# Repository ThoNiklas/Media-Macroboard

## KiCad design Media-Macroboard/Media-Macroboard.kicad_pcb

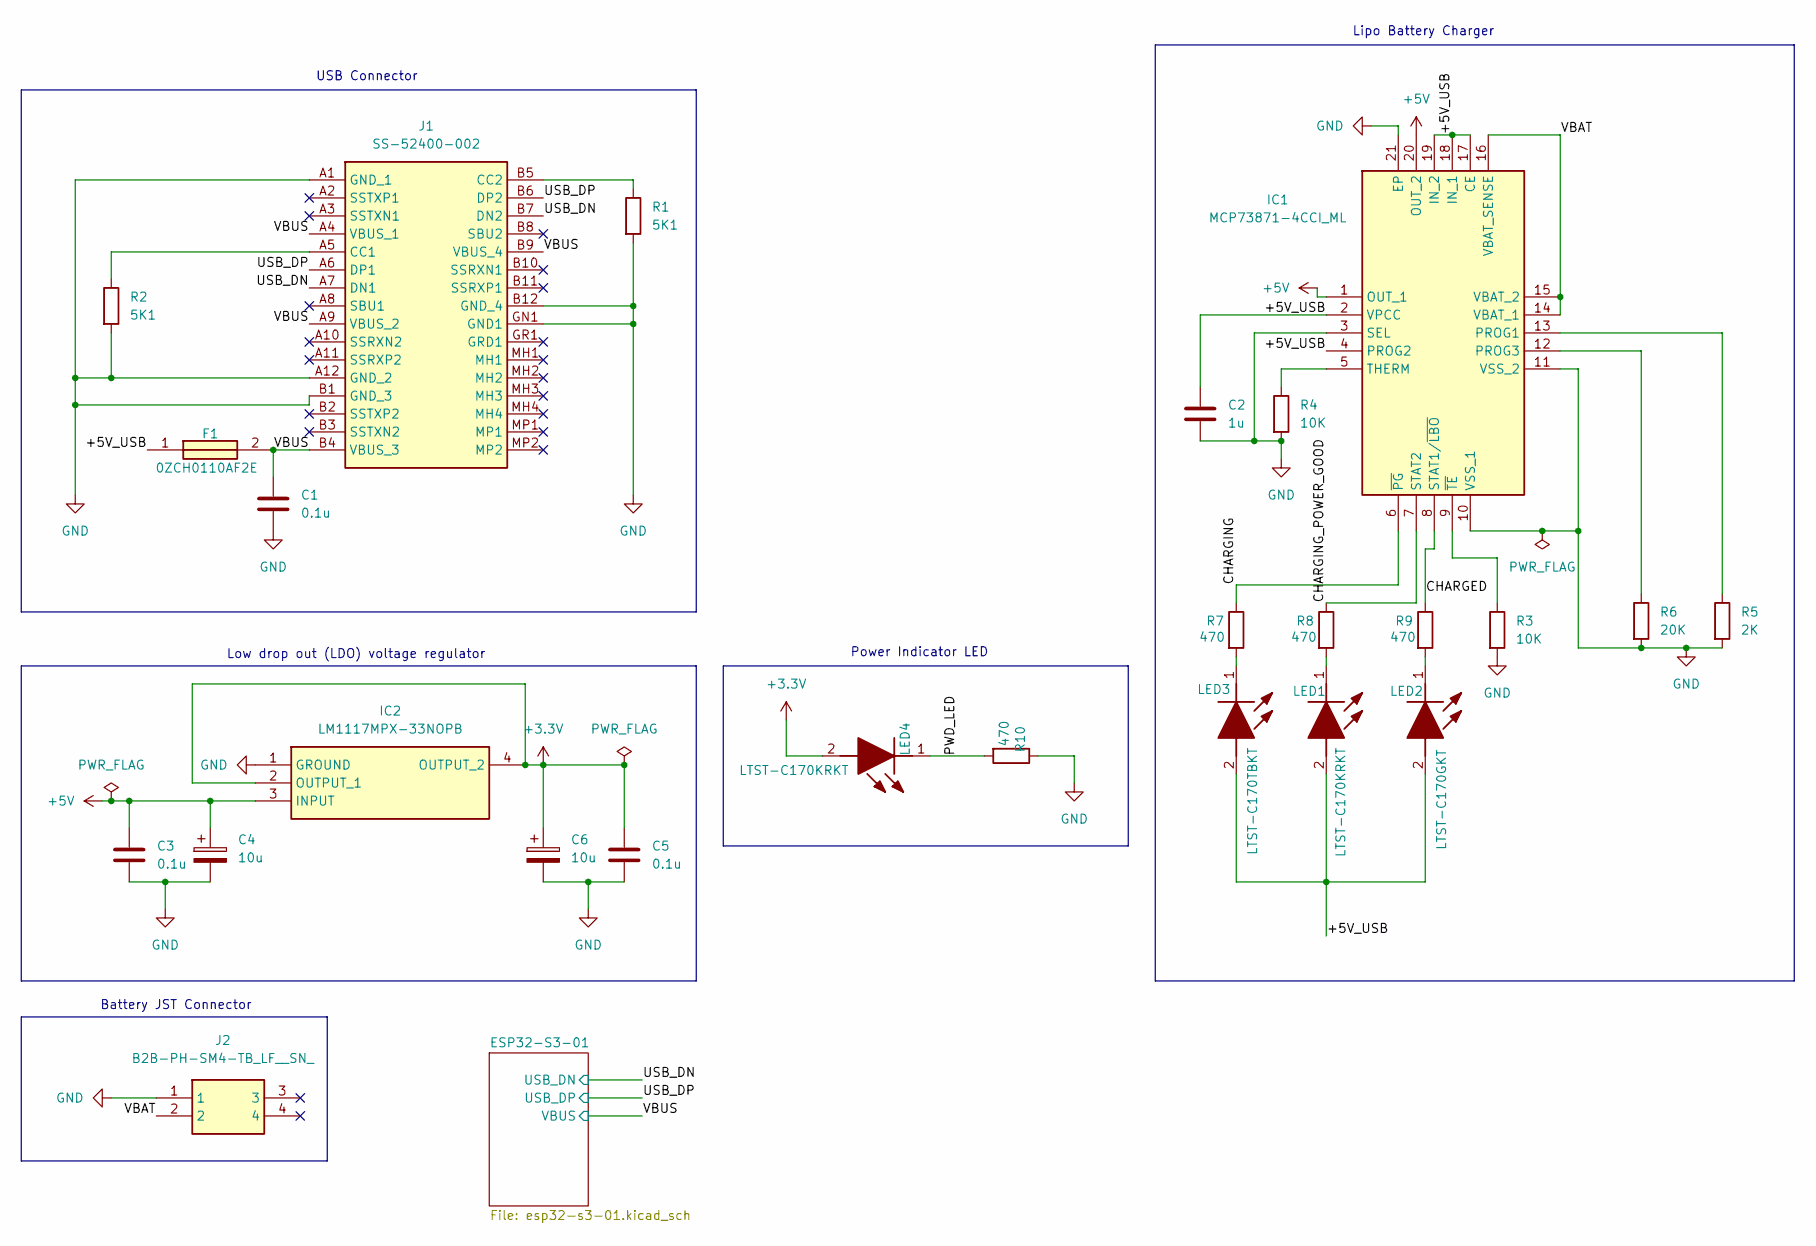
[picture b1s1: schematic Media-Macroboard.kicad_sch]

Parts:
C1, C3, C5: 0.1u; C_0805_2012Metric_Pad1.18x1.45mm_HandSolder
C2: 1u; C_0805_2012Metric_Pad1.18x1.45mm_HandSolder
C4, C6: 10u; C_1206_3216Metric
F1: 0ZCH0110AF2E; FUSC3226X100N; Manufacturer_Part_Number 0ZCH0110AF2E
IC1: MCP73871-4CCI_ML; QFN50P400X400X100-21N-D; Mouser Part Number 579-MCP73871-4CCI/ML
IC2: LM1117MPX-33NOPB; SOT230P700X180-4N; Mouser Part Number 863-LM1117MPX-33NOPB
J1: SS-52400-002; SS52400002; Mouser Part Number 530-SS-52400-002
J2: B2B-PH-SM4-TB_LF__SN_; B2BPHSM4TBLFSN; Mouser Part Number N/A
LED1, LED4: LTST-C170KRKT; LEDC2012X120N; Mouser Part Number 859-LTST-C170KRKT
LED2: LTST-C170GKT; LEDC2012X120N; Mouser Part Number 859-LTST-C170GKT
LED3: LTST-C170TBKT; LEDC2012X120N; Mouser Part Number 859-LTST-C170TBKT
R1, R2: 5K1; R_0805_2012Metric_Pad1.20x1.40mm_HandSolder
R3, R4: 10K; R_0805_2012Metric_Pad1.20x1.40mm_HandSolder
R5: 2K; R_0805_2012Metric_Pad1.20x1.40mm_HandSolder
R6: 20K; R_0805_2012Metric_Pad1.20x1.40mm_HandSolder
R7, R8, R9, R10: 470; R_0805_2012Metric_Pad1.20x1.40mm_HandSolder

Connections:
+3.3V: C5.1, C6.1, IC2.2 (OUTPUT_1), IC2.4 (OUTPUT_2), LED4.2 (A); also elsewhere on the board
+5V: C3.1, C4.1, IC1.1 (OUT_1), IC1.20 (OUT_2), IC2.3 (INPUT)
/+5V_USB: C2.1, F1.1, IC1.2 (VPCC), IC1.4 (PROG2), IC1.17 (CE), IC1.18 (IN_1), IC1.19 (IN_2), LED1.2 (A), LED2.2 (A), LED3.2 (A)
/CHARGED: IC1.8 (STAT1/~LBO), R9.1
/CHARGING: IC1.6 (~PG), R7.1
/CHARGING_POWER_GOOD: IC1.7 (STAT2), R8.1
/PWD_LED: LED4.1 (K), R10.2
/USB_DN: J1.A7 (DN1), J1.B7 (DN2); also elsewhere on the board
/USB_DP: J1.A6 (DP1), J1.B6 (DP2); also elsewhere on the board
/VBAT: IC1.14 (VBAT_1), IC1.15 (VBAT_2), IC1.16 (VBAT_SENSE), J2.2
/VBUS: C1.1, F1.2, J1.A4 (VBUS_1), J1.A9 (VBUS_2), J1.B4 (VBUS_3), J1.B9 (VBUS_4); also elsewhere on the board
GND: C1.2, C2.2, C3.2, C4.2, C5.2, C6.2, IC1.3 (SEL), IC1.10 (VSS_1), IC1.11 (VSS_2), IC1.21 (EP), IC2.1 (GROUND), J1.A1 (GND_1), J1.A12 (GND_2), J1.B1 (GND_3), J1.B12 (GND_4), J1.GN1 (GND1), J2.1, R1.2, R2.2, R3.2, R4.2, R5.2, R6.2, R10.1; also elsewhere on the board
unnamed: IC1.13 (PROG1), R5.1
unnamed: IC1.12 (PROG3), R6.1
unnamed: IC1.5 (THERM), R4.1
unnamed: IC1.9 (~TE), R3.1
unnamed: J1.A5 (CC1), R2.1
unnamed: J1.B5 (CC2), R1.1
unnamed: LED1.1 (K), R8.2
unnamed: LED2.1 (K), R9.2
unnamed: LED3.1 (K), R7.2

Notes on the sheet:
USB Connector
Lipo Battery Charger
Power Indicator LED
Battery JST Connector
Low drop out (LDO) voltage regulator

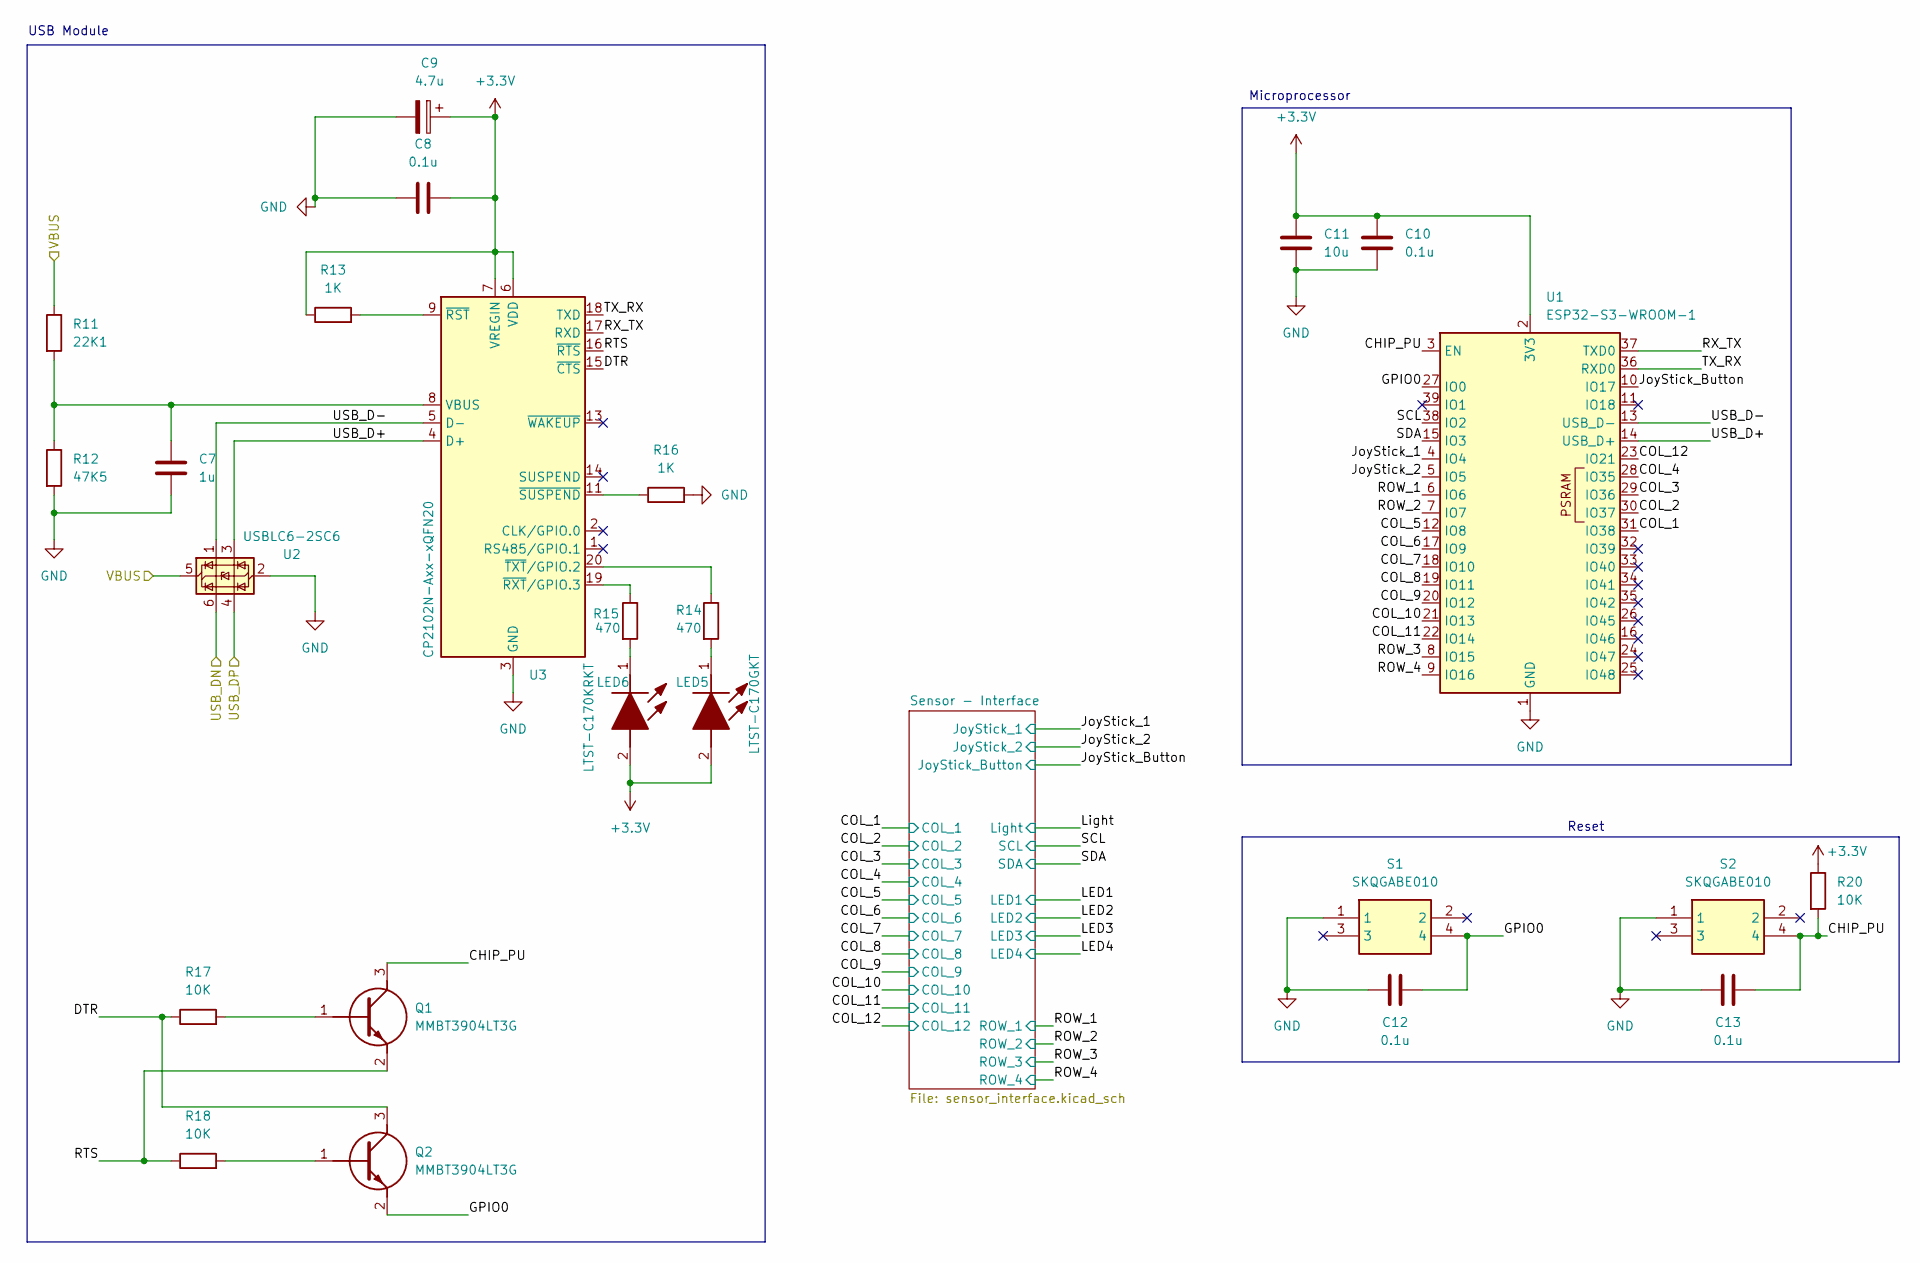
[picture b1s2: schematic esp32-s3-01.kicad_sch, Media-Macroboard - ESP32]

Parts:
C7: 1u; C_0805_2012Metric_Pad1.18x1.45mm_HandSolder
C8, C10, C12, C13: 0.1u; C_0805_2012Metric_Pad1.18x1.45mm_HandSolder
C9: 4.7u; C_1206_3216Metric
C11: 10u; C_0805_2012Metric_Pad1.18x1.45mm_HandSolder
LED5: LTST-C170GKT; LEDC2012X120N; Mouser Part Number 859-LTST-C170GKT
LED6: LTST-C170KRKT; LEDC2012X120N; Mouser Part Number 859-LTST-C170KRKT
Q1, Q2: MMBT3904LT3G; SOT96P237X111-3N; Mouser Part Number 863-MMBT3904LT3G
R11: 22K1; R_0805_2012Metric_Pad1.20x1.40mm_HandSolder
R12: 47K5; R_0805_2012Metric_Pad1.20x1.40mm_HandSolder
R13, R16: 1K; R_0805_2012Metric_Pad1.20x1.40mm_HandSolder
R14, R15: 470; R_0805_2012Metric_Pad1.20x1.40mm_HandSolder
R17, R18, R20: 10K; R_0805_2012Metric_Pad1.20x1.40mm_HandSolder
S1, S2: SKQGABE010; SKQGAKE010; Mouser Part Number 688-SKQGAB
U1: ESP32-S3-WROOM-1
U2: USBLC6-2SC6; SOT-23-6
U3: CP2102N-Axx-xQFN20; CP2102NA02GQFN20

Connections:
+3.3V: C8.2, C9.1, C10.1, C11.1, LED5.2 (A), LED6.2 (A), R13.1, R20.1, U1.2 (3V3), U3.6 (VDD), U3.7 (VREGIN); also elsewhere on the board
/ESP32-S3-01/CHIP_PU: C13.1, Q1.3 (C), R20.2, S2.4, U1.3 (EN)
/ESP32-S3-01/COL_1: U1.31 (IO38); also elsewhere on the board
/ESP32-S3-01/COL_2: U1.30 (IO37); also elsewhere on the board
/ESP32-S3-01/COL_3: U1.29 (IO36); also elsewhere on the board
/ESP32-S3-01/COL_4: U1.28 (IO35); also elsewhere on the board
/ESP32-S3-01/COL_5: U1.12 (IO8); also elsewhere on the board
/ESP32-S3-01/COL_6: U1.17 (IO9); also elsewhere on the board
/ESP32-S3-01/COL_7: U1.18 (IO10); also elsewhere on the board
/ESP32-S3-01/COL_8: U1.19 (IO11); also elsewhere on the board
/ESP32-S3-01/COL_9: U1.20 (IO12); also elsewhere on the board
/ESP32-S3-01/COL_10: U1.21 (IO13); also elsewhere on the board
/ESP32-S3-01/COL_11: U1.22 (IO14); also elsewhere on the board
/ESP32-S3-01/COL_12: U1.23 (IO21); also elsewhere on the board
/ESP32-S3-01/DTR: Q2.3 (C), R17.1, U3.15 (~CTS)
/ESP32-S3-01/GPIO0: C12.1, Q2.2 (E), S1.4, U1.27 (IO0)
/ESP32-S3-01/JoyStick_1: U1.4 (IO4); also elsewhere on the board
/ESP32-S3-01/JoyStick_2: U1.5 (IO5); also elsewhere on the board
/ESP32-S3-01/JoyStick_Button: U1.10 (IO17); also elsewhere on the board
/ESP32-S3-01/ROW_1: U1.6 (IO6); also elsewhere on the board
/ESP32-S3-01/ROW_2: U1.7 (IO7); also elsewhere on the board
/ESP32-S3-01/ROW_3: U1.8 (IO15); also elsewhere on the board
/ESP32-S3-01/ROW_4: U1.9 (IO16); also elsewhere on the board
/ESP32-S3-01/RTS: Q1.2 (E), R18.1, U3.16 (~RTS)
/ESP32-S3-01/RX_TX: U1.37 (TXD0), U3.17 (RXD)
/ESP32-S3-01/SCL: U1.38 (IO2); also elsewhere on the board
/ESP32-S3-01/SDA: U1.15 (IO3); also elsewhere on the board
/ESP32-S3-01/TX_RX: U1.36 (RXD0), U3.18 (TXD)
/ESP32-S3-01/USB_D+: U1.14 (USB_D+), U2.3 (I/O2), U3.4 (D+)
/ESP32-S3-01/USB_D-: U1.13 (USB_D-), U2.1 (I/O1), U3.5 (D-)
/USB_DN: U2.6 (I/O1); also elsewhere on the board
/USB_DP: U2.4 (I/O2); also elsewhere on the board
/VBUS: R11.1, U2.5 (VBUS); also elsewhere on the board
GND: C7.2, C8.1, C9.2, C10.2, C11.2, C12.2, C13.2, R12.2, R16.2, S1.1, S2.1, U1.1 (GND), U1.40 (GND), U1.41 (GND), U2.2 (GND), U3.3 (GND), U3.12 (GND), U3.21 (GND); also elsewhere on the board
unnamed: LED5.1 (K), R14.2
unnamed: LED6.1 (K), R15.2
unnamed: Q1.1 (B), R17.2
unnamed: Q2.1 (B), R18.2
unnamed: C7.1, R11.2, R12.1, U3.8 (VBUS)
unnamed: R13.2, U3.9 (~RST)
unnamed: R15.1, U3.19 (~RXT/GPIO.3)
unnamed: R16.1, U3.11 (~SUSPEND)
unnamed: R14.1, U3.20 (~TXT/GPIO.2)

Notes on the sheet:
Microprocessor
Reset
USB Module

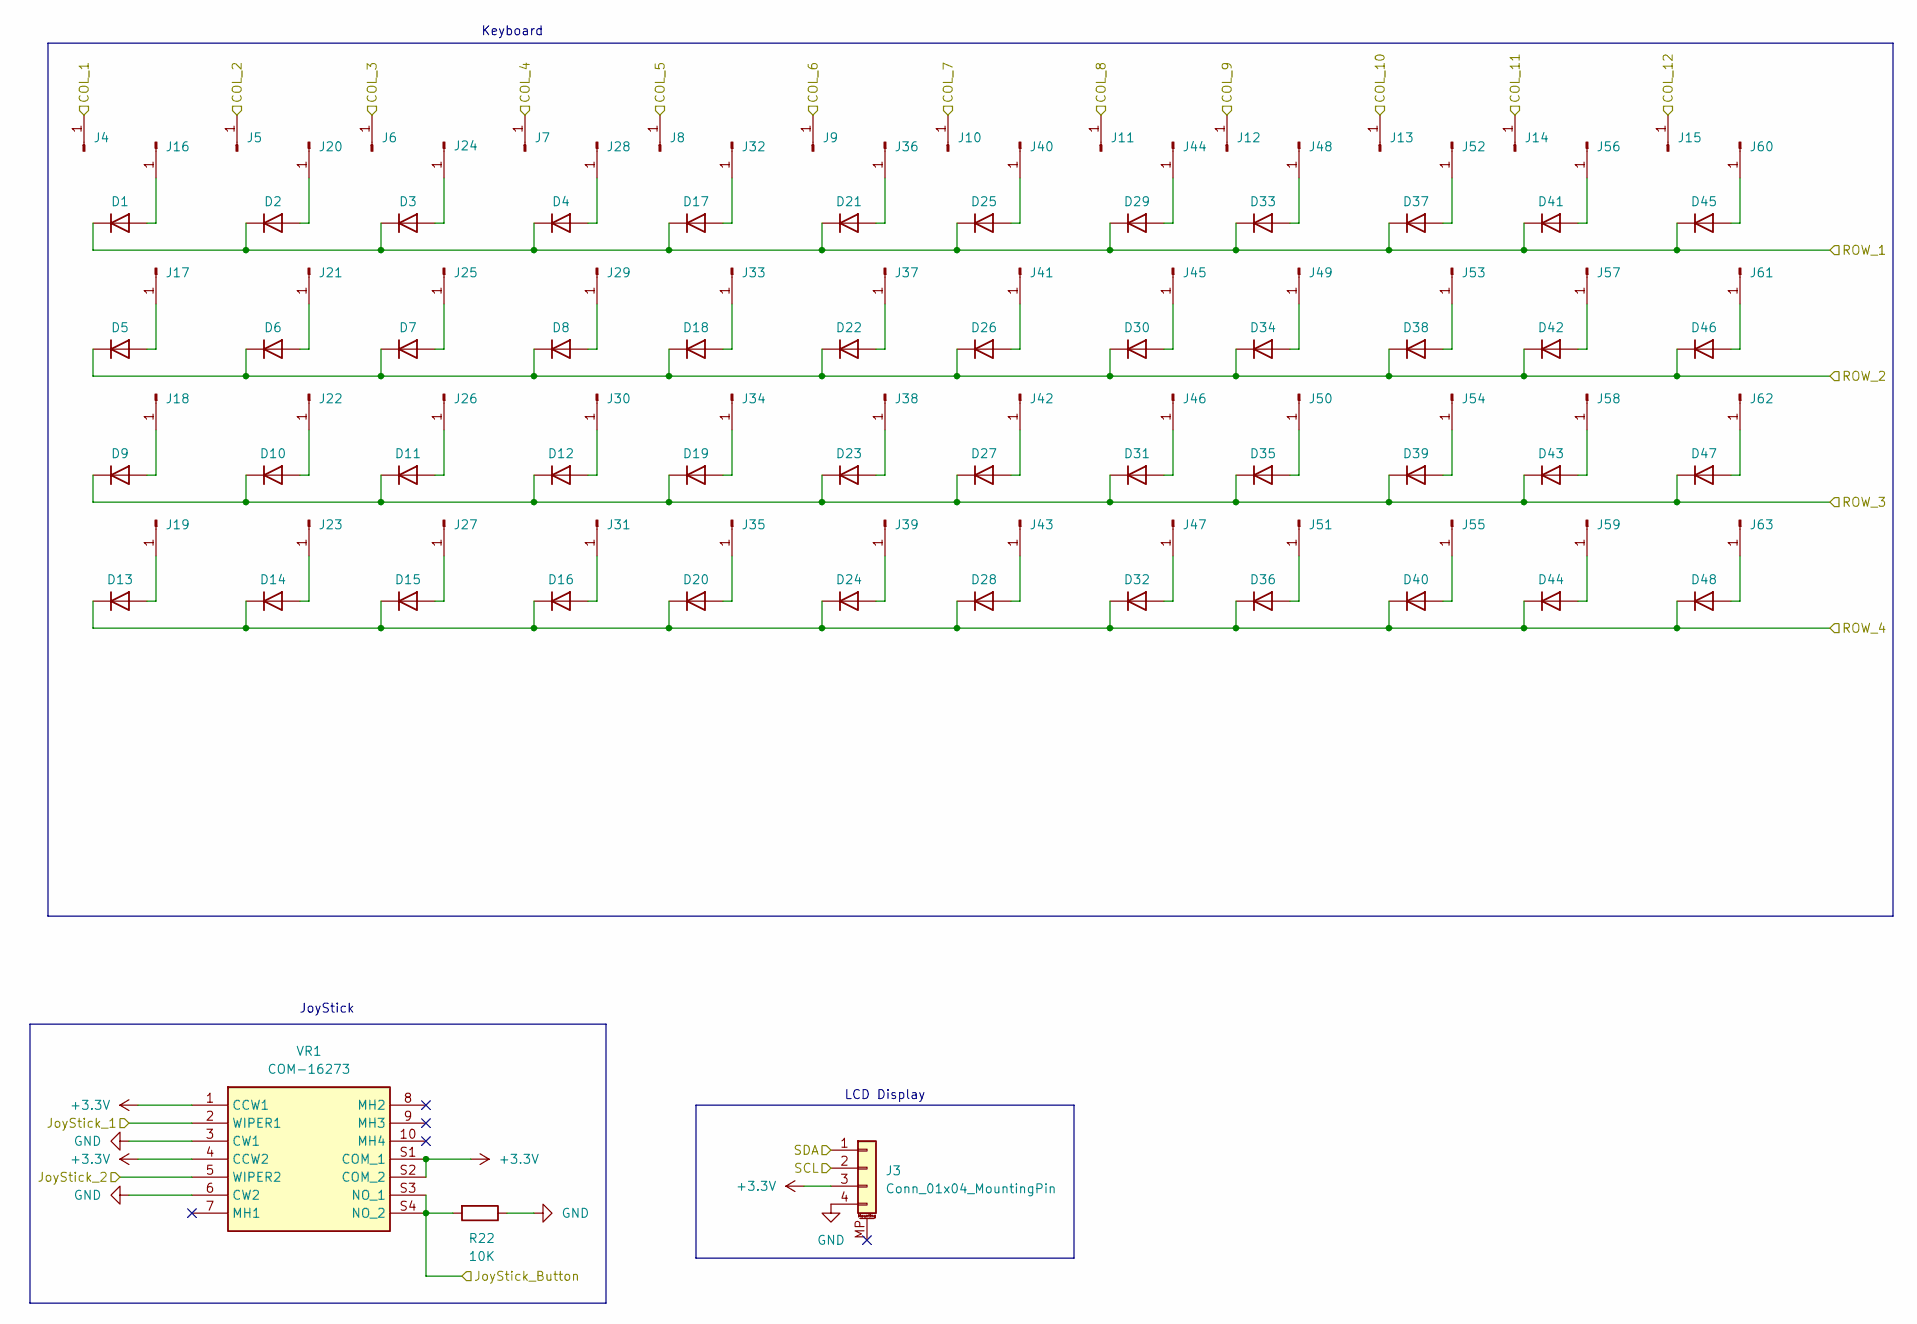
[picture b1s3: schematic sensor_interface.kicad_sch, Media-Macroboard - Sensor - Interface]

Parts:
D1, D2, D3, D4, D5, D6, D7, D8, D9, D10, D11, D12, D13, D14, D15, D16, D17, D18, D19, D20, D21, D22, D23, D24, D25, D26, D27, D28, D29, D30, D31, D32, D33, D34, D35, D36, D37, D38, D39, D40, D41, D42, D43, D44, D45, D46, D47, D48: D; D_0805_2012Metric_Pad1.15x1.40mm_HandSolder
J3: Conn_01x04_MountingPin; PinHeader_1x04_P2.54mm_Vertical
J4, J5, J6, J7, J8, J9, J10, J11, J12, J13, J14, J15, J16, J17, J18, J19, J20, J21, J22, J23, J24, J25, J26, J27, J28, J29, J30, J31, J32, J33, J34, J35, J36, J37, J38, J39, J40, J41, J42, J43, J44, J45, J46, J47, J48, J49, J50, J51, J52, J53, J54, J55, J56, J57, J58, J59, J60, J61, J62, J63: Conn_01x01_Pin; PinHeader_1x01_P1.00mm_Vertical
R22: 10K; R_0805_2012Metric_Pad1.20x1.40mm_HandSolder
VR1: COM-16273; COM16273; Mouser Part Number 474-COM-16273

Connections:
+3.3V: J3.3, VR1.1 (CCW1), VR1.4 (CCW2), VR1.S1 (COM_1), VR1.S2 (COM_2); also elsewhere on the board
/ESP32-S3-01/COL_1: J4.1; also elsewhere on the board
/ESP32-S3-01/COL_2: J5.1; also elsewhere on the board
/ESP32-S3-01/COL_3: J6.1; also elsewhere on the board
/ESP32-S3-01/COL_4: J7.1; also elsewhere on the board
/ESP32-S3-01/COL_5: J8.1; also elsewhere on the board
/ESP32-S3-01/COL_6: J9.1; also elsewhere on the board
/ESP32-S3-01/COL_7: J10.1; also elsewhere on the board
/ESP32-S3-01/COL_8: J11.1; also elsewhere on the board
/ESP32-S3-01/COL_9: J12.1; also elsewhere on the board
/ESP32-S3-01/COL_10: J13.1; also elsewhere on the board
/ESP32-S3-01/COL_11: J14.1; also elsewhere on the board
/ESP32-S3-01/COL_12: J15.1; also elsewhere on the board
/ESP32-S3-01/JoyStick_1: VR1.2 (WIPER1); also elsewhere on the board
/ESP32-S3-01/JoyStick_2: VR1.5 (WIPER2); also elsewhere on the board
/ESP32-S3-01/JoyStick_Button: R22.2, VR1.S3 (NO_1), VR1.S4 (NO_2); also elsewhere on the board
/ESP32-S3-01/ROW_1: D1.1 (K), D2.1 (K), D3.1 (K), D4.1 (K), D17.1 (K), D21.1 (K), D25.1 (K), D29.1 (K), D33.1 (K), D37.1 (K), D41.1 (K), D45.1 (K); also elsewhere on the board
/ESP32-S3-01/ROW_2: D5.1 (K), D6.1 (K), D7.1 (K), D8.1 (K), D18.1 (K), D22.1 (K), D26.1 (K), D30.1 (K), D34.1 (K), D38.1 (K), D42.1 (K), D46.1 (K); also elsewhere on the board
/ESP32-S3-01/ROW_3: D9.1 (K), D10.1 (K), D11.1 (K), D12.1 (K), D19.1 (K), D23.1 (K), D27.1 (K), D31.1 (K), D35.1 (K), D39.1 (K), D43.1 (K), D47.1 (K); also elsewhere on the board
/ESP32-S3-01/ROW_4: D13.1 (K), D14.1 (K), D15.1 (K), D16.1 (K), D20.1 (K), D24.1 (K), D28.1 (K), D32.1 (K), D36.1 (K), D40.1 (K), D44.1 (K), D48.1 (K); also elsewhere on the board
/ESP32-S3-01/SCL: J3.2; also elsewhere on the board
/ESP32-S3-01/SDA: J3.1; also elsewhere on the board
GND: J3.4, R22.1, VR1.3 (CW1), VR1.6 (CW2); also elsewhere on the board
unnamed: D1.2 (A), J16.1
unnamed: D2.2 (A), J20.1
unnamed: D3.2 (A), J24.1
unnamed: D4.2 (A), J28.1
unnamed: D5.2 (A), J17.1
unnamed: D6.2 (A), J21.1
unnamed: D7.2 (A), J25.1
unnamed: D8.2 (A), J29.1
unnamed: D9.2 (A), J18.1
unnamed: D10.2 (A), J22.1
unnamed: D11.2 (A), J26.1
unnamed: D12.2 (A), J30.1
unnamed: D13.2 (A), J19.1
unnamed: D14.2 (A), J23.1
unnamed: D15.2 (A), J27.1
unnamed: D16.2 (A), J31.1
unnamed: D17.2 (A), J32.1
unnamed: D18.2 (A), J33.1
unnamed: D19.2 (A), J34.1
unnamed: D20.2 (A), J35.1
unnamed: D21.2 (A), J36.1
unnamed: D22.2 (A), J37.1
unnamed: D23.2 (A), J38.1
unnamed: D24.2 (A), J39.1
unnamed: D25.2 (A), J40.1
unnamed: D26.2 (A), J41.1
unnamed: D27.2 (A), J42.1
unnamed: D28.2 (A), J43.1
unnamed: D29.2 (A), J44.1
unnamed: D30.2 (A), J45.1
unnamed: D31.2 (A), J46.1
unnamed: D32.2 (A), J47.1
unnamed: D33.2 (A), J48.1
unnamed: D34.2 (A), J49.1
unnamed: D35.2 (A), J50.1
unnamed: D36.2 (A), J51.1
unnamed: D37.2 (A), J52.1
unnamed: D38.2 (A), J53.1
unnamed: D39.2 (A), J54.1
unnamed: D40.2 (A), J55.1
unnamed: D41.2 (A), J56.1
unnamed: D42.2 (A), J57.1
unnamed: D43.2 (A), J58.1
unnamed: D44.2 (A), J59.1
unnamed: D45.2 (A), J60.1
unnamed: D46.2 (A), J61.1
unnamed: D47.2 (A), J62.1
unnamed: D48.2 (A), J63.1

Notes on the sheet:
Keyboard
JoyStick
LCD Display

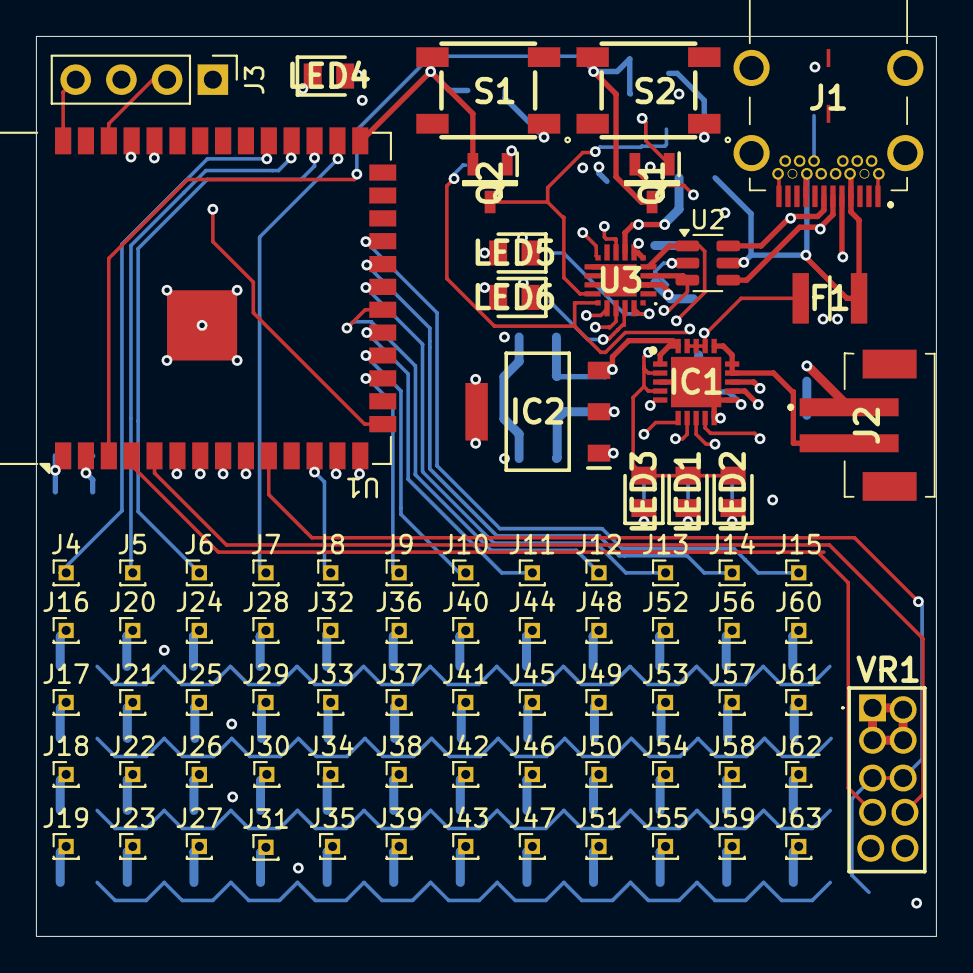
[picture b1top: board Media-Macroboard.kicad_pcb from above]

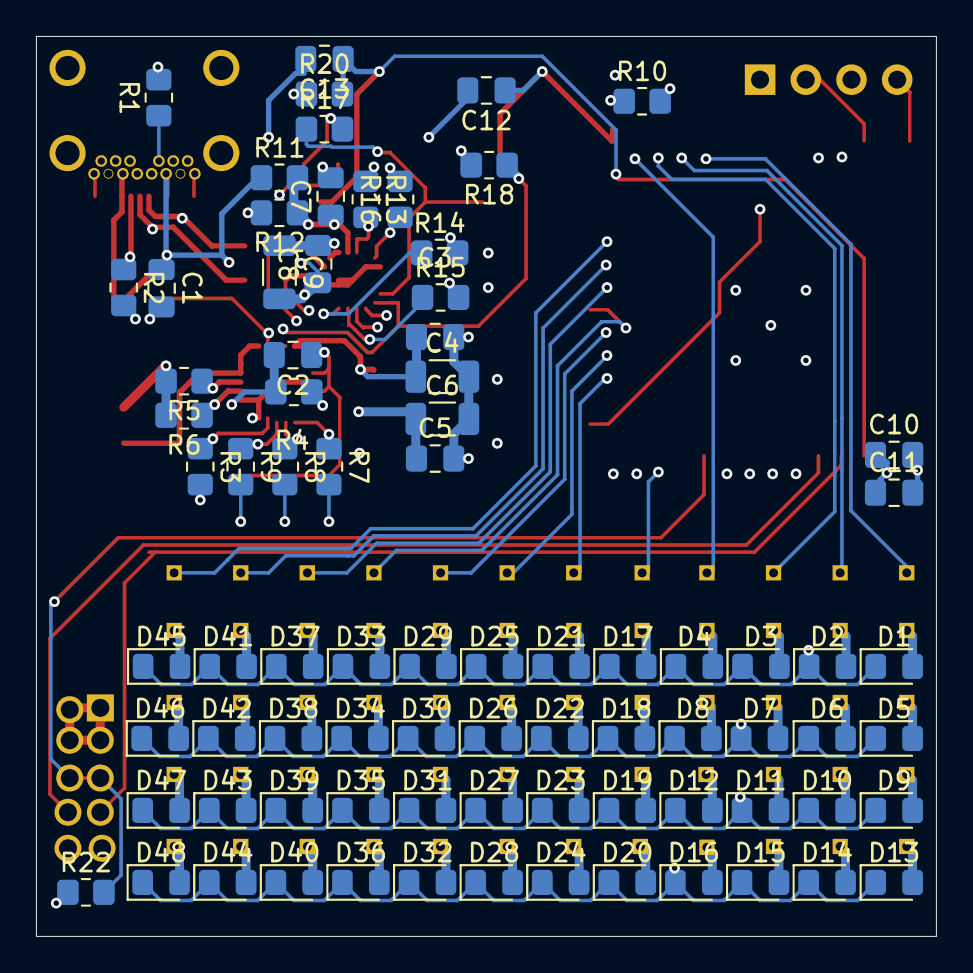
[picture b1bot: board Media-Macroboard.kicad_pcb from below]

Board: 4 copper layers, 50.0 x 50.0 mm, 161 parts (81 on the bottom side), 107 nets.

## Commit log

2025-03-23 First productable version
2025-04-12 Made four-layer version
2025-04-17 Added more rows and columns
